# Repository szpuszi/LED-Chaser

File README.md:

# LED-Chaser
LED-Chaser is an Circular-shaped PCB, with WS2812B LEDs. It has built-in microphone so it can be reactive to music.

## How it works?
- Brain: It uses ATtiny85, which sends PWM signals to the WS2812B, receives data from the potentiometer and microphone.
- Power: We power it by USB-C.
- LEDs: The first pin of the first WS2812B receives data from ATtiny85 and forwards to the second WS2812B. The second LED does the same, all the way to the 24rd LED, it's output is floating.

# BOM
Click [here](/BOM.csv)

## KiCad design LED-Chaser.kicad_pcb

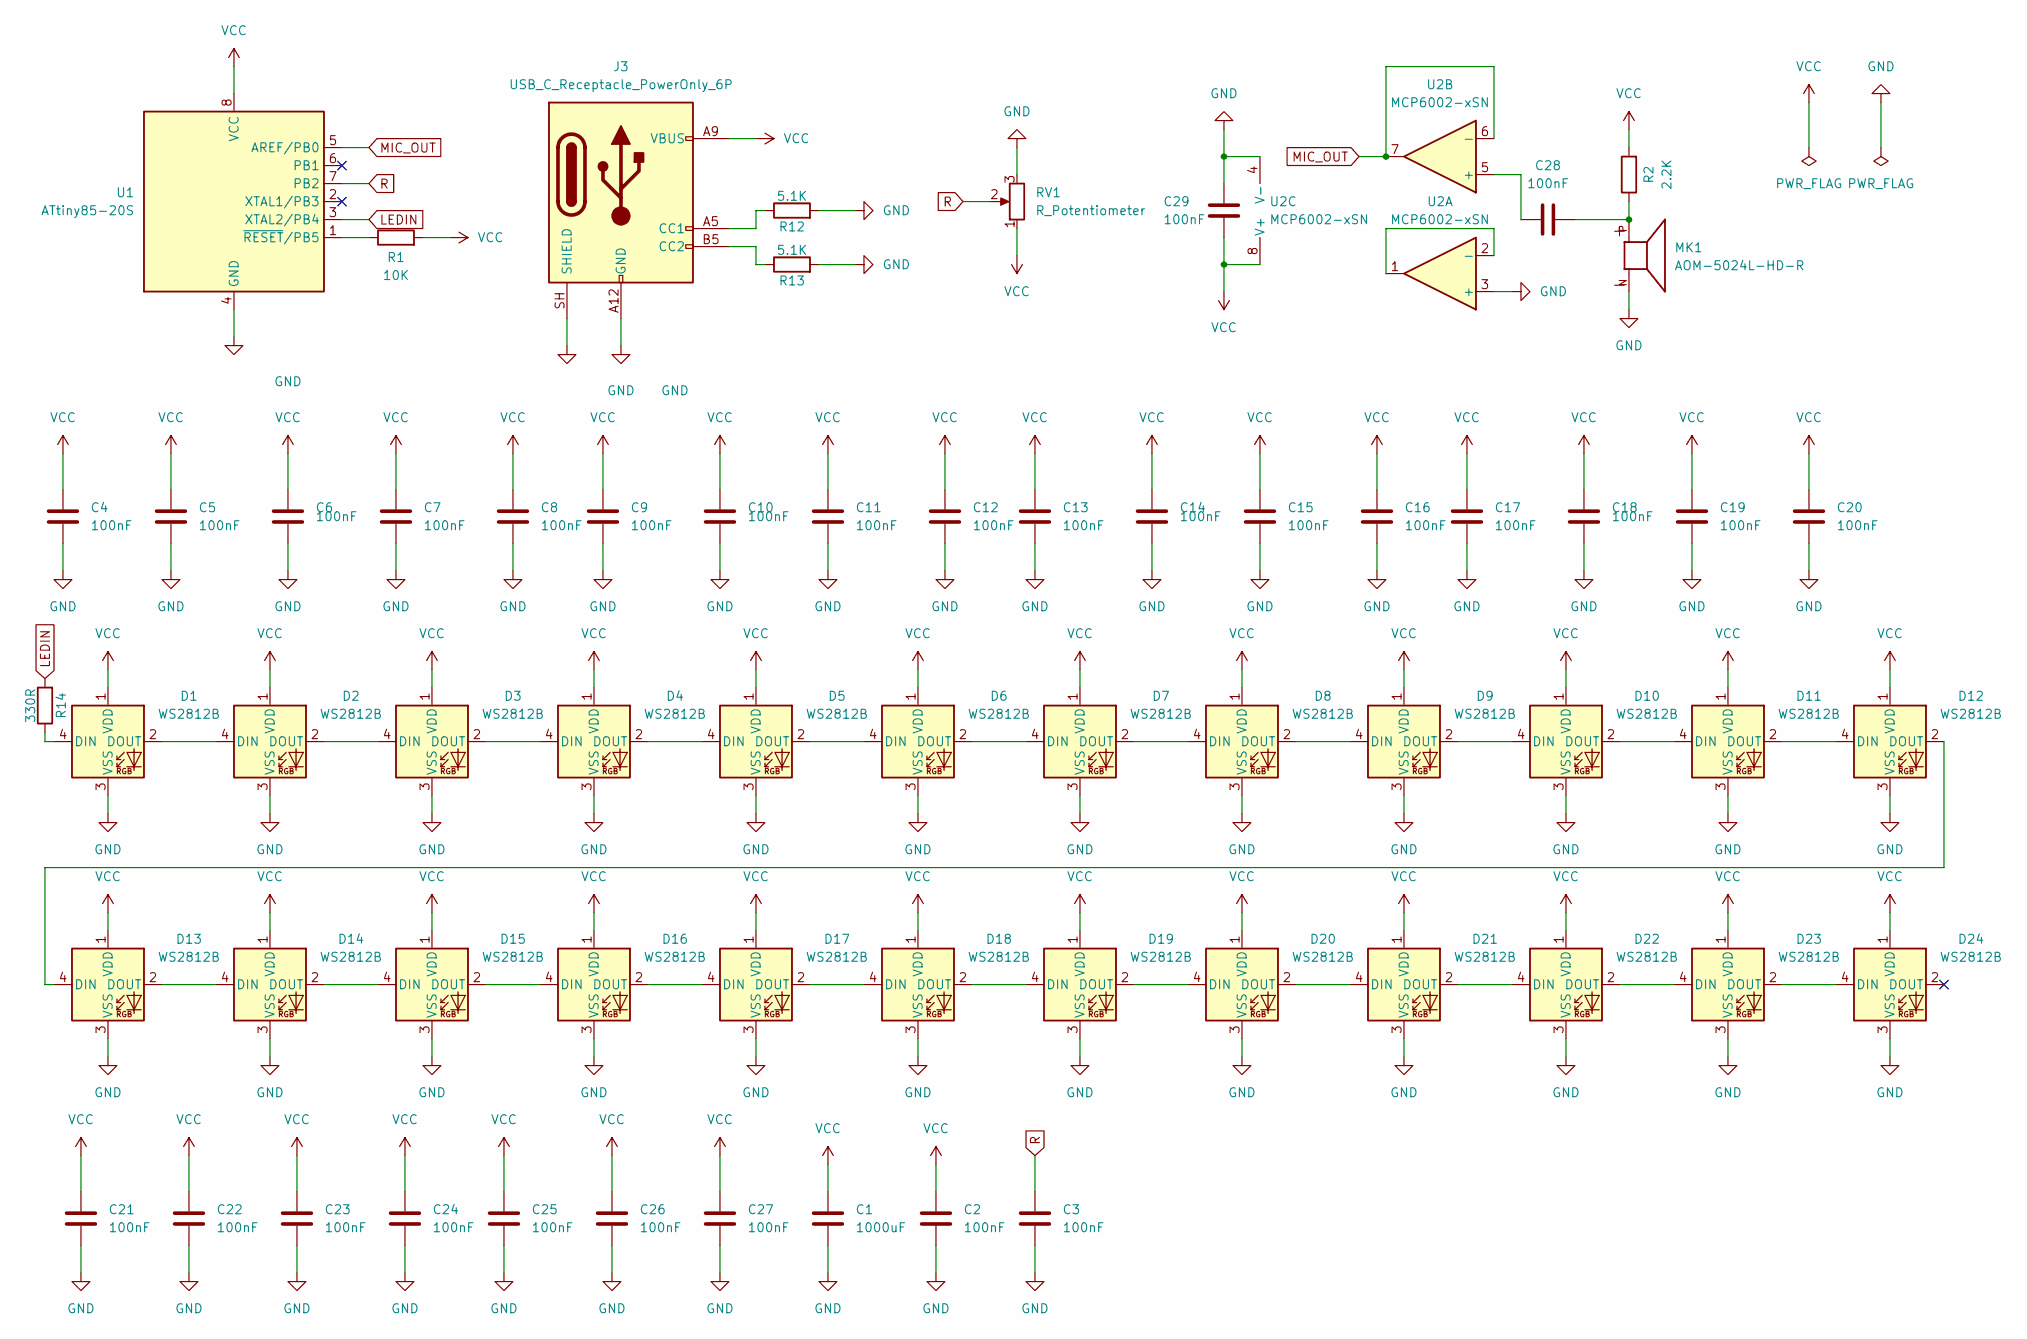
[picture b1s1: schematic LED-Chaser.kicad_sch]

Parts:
C1: 1000uF; CP_Elec_10x10.5
C2, C3, C4, C5, C6, C7, C8, C9, C10, C11, C12, C13, C14, C15, C16, C17, C18, C19, C20, C21, C22, C23, C24, C25, C26, C27, C28, C29: 100nF; C_0603_1608Metric
D1, D2, D3, D4, D5, D6, D7, D8, D9, D10, D11, D12, D13, D14, D15, D16, D17, D18, D19, D20, D21, D22, D23, D24: WS2812B; LED_WS2812B_PLCC4_5.0x5.0mm_P3.2mm
J3: USB_C_Receptacle_PowerOnly_6P; USB_C_Receptacle_GCT_USB4125-xx-x_6P_TopMnt_Horizontal
MK1: AOM-5024L-HD-R; MIC_AOM-5024L-HD-R; PARTREV A
R1: 10K; R_0603_1608Metric
R2: 2.2K; R_0603_1608Metric
R12, R13: 5.1K; R_0603_1608Metric
R14: 330R; R_0603_1608Metric
RV1: R_Potentiometer; Potentiometer_Alps_RK09K_Single_Horizontal
U1: ATtiny85-20S; SOIC-8_5.3x5.3mm_P1.27mm
U2: MCP6002-xSN; SOIC-8_3.9x4.9mm_P1.27mm

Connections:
GND: C1.2, C2.2, C3.2, C4.2, C5.2, C6.2, C7.2, C8.2, C9.2, C10.2, C11.2, C12.2, C13.2, C14.2, C15.2, C16.2, C17.2, C18.2, C19.2, C20.2, C21.2, C22.2, C23.2, C24.2, C25.2, C26.2, C27.2, C29.1, D1.3 (VSS), D2.3 (VSS), D3.3 (VSS), D4.3 (VSS), D5.3 (VSS), D6.3 (VSS), D7.3 (VSS), D8.3 (VSS), D9.3 (VSS), D10.3 (VSS), D11.3 (VSS), D12.3 (VSS), D13.3 (VSS), D14.3 (VSS), D15.3 (VSS), D16.3 (VSS), D17.3 (VSS), D18.3 (VSS), D19.3 (VSS), D20.3 (VSS), D21.3 (VSS), D22.3 (VSS), D23.3 (VSS), D24.3 (VSS), J3.A12 (GND), J3.B12 (GND), J3.SH (SHIELD), MK1.N, R12.2, R13.2, RV1.3, U1.4 (GND), U2.3 (+), U2.4 (V-)
LEDIN: R14.2, U1.3 (XTAL2/PB4)
MIC_OUT: U1.5 (AREF/PB0), U2.6 (-), U2.7
unnamed: C28.2, MK1.P, R2.1
unnamed: D1.4 (DIN), R14.1
unnamed: D1.2 (DOUT), D2.4 (DIN)
unnamed: D2.2 (DOUT), D3.4 (DIN)
unnamed: D3.2 (DOUT), D4.4 (DIN)
unnamed: D4.2 (DOUT), D5.4 (DIN)
unnamed: D5.2 (DOUT), D6.4 (DIN)
unnamed: D6.2 (DOUT), D7.4 (DIN)
unnamed: D7.2 (DOUT), D8.4 (DIN)
unnamed: D8.2 (DOUT), D9.4 (DIN)
unnamed: D9.2 (DOUT), D10.4 (DIN)
unnamed: D10.2 (DOUT), D11.4 (DIN)
unnamed: D11.2 (DOUT), D12.4 (DIN)
unnamed: D12.2 (DOUT), D13.4 (DIN)
unnamed: D13.2 (DOUT), D14.4 (DIN)
unnamed: D14.2 (DOUT), D15.4 (DIN)
unnamed: D15.2 (DOUT), D16.4 (DIN)
unnamed: D16.2 (DOUT), D17.4 (DIN)
unnamed: D17.2 (DOUT), D18.4 (DIN)
unnamed: D18.2 (DOUT), D19.4 (DIN)
unnamed: D19.2 (DOUT), D20.4 (DIN)
unnamed: D20.2 (DOUT), D21.4 (DIN)
unnamed: D21.2 (DOUT), D22.4 (DIN)
unnamed: D22.2 (DOUT), D23.4 (DIN)
unnamed: D23.2 (DOUT), D24.4 (DIN)
unnamed: J3.A5 (CC1), R12.1
unnamed: J3.B5 (CC2), R13.1
unnamed: R1.1, U1.1 (~RESET/PB5)
unnamed: U2.1, U2.2 (-)
unnamed: C28.1, U2.5 (+)
R: C3.1, RV1.2, U1.7 (PB2)
VCC: C1.1, C2.1, C4.1, C5.1, C6.1, C7.1, C8.1, C9.1, C10.1, C11.1, C12.1, C13.1, C14.1, C15.1, C16.1, C17.1, C18.1, C19.1, C20.1, C21.1, C22.1, C23.1, C24.1, C25.1, C26.1, C27.1, C29.2, D1.1 (VDD), D2.1 (VDD), D3.1 (VDD), D4.1 (VDD), D5.1 (VDD), D6.1 (VDD), D7.1 (VDD), D8.1 (VDD), D9.1 (VDD), D10.1 (VDD), D11.1 (VDD), D12.1 (VDD), D13.1 (VDD), D14.1 (VDD), D15.1 (VDD), D16.1 (VDD), D17.1 (VDD), D18.1 (VDD), D19.1 (VDD), D20.1 (VDD), D21.1 (VDD), D22.1 (VDD), D23.1 (VDD), D24.1 (VDD), J3.A9 (VBUS), J3.B9 (VBUS), R1.2, R2.2, RV1.1, U1.8 (VCC), U2.8 (V+)

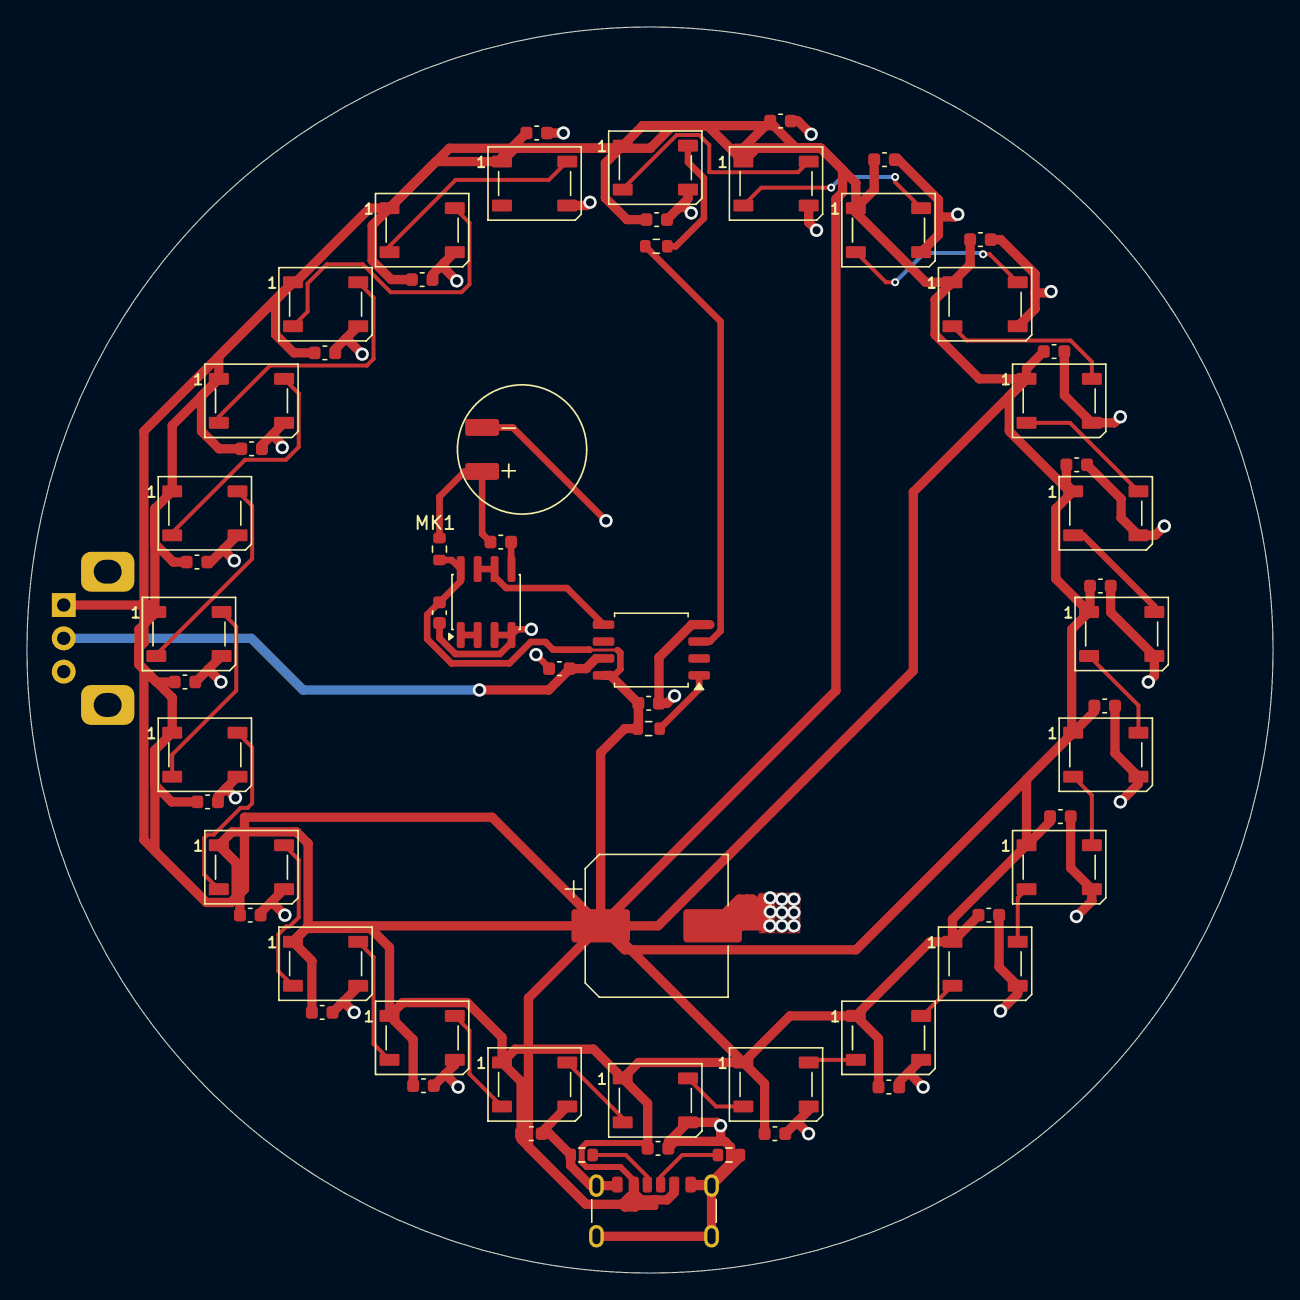
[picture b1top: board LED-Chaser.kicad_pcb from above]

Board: 2 copper layers, 93.5 x 93.5 mm, 63 parts (0 on the bottom side), 35 nets.

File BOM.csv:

Reference,Qty,Value,Link
C1,1,1000uF,https://www.tme.eu/pl/details/eeeft1c102ap/kondensatory-elek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
"C2,C3,C4,C5,C6,C7,C8,C9,C10,C11,C12,C13,C14,C15,C16,C17,C18,C19,C20,C21,C22,C23,C24,C25,C26,C27,C28,C29",28,100nF,https://www.tme.eu/pl/details/cl10b104ka8nnnc/kondensatory-m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
"D1,D2,D3,D4,D5,D6,D7,D8,D9,D10,D11,D12,D13,D14,D15,D16,D17,D18,D19,D20,D21,D22,D23,D24",24,WS2812B,https://www.tme.eu/pl/details/ws2812b-v5/diody-led-smd-kolor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
J3,1,USB_C_Receptacle_PowerOnly_6P,https://www.tme.eu/pl/details/usb4125-gf-a-0190/zlacza-usb-i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
MK1,1,AOM-5024L-HD-R,https://www.tme.eu/pl/details/aom-5024l-hd-r/mikrofony-i-slu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
R1,1,10K,https://www.tme.eu/pl/details/crcw060310k0fkea/rezystory-smd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
R2,1,2.2K,https://www.tme.eu/pl/details/crcw06032k20fkea/rezystory-smd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
"R12,R13",2,5.1K,https://www.tme.eu/pl/details/rca06035k10fkea/rezystory-smd/vishay/
R14,1,330R,https://www.tme.eu/pl/details/rca0603330rfkea/rezystory-smd/vishay/
RV1,1,R_Potentiometer,https://www.tme.eu/pl/details/rk09k1110a0j/potencjometry-jed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
U1,1,ATtiny85-20S,https://www.tme.eu/pl/details/attiny85-20sf/rodzina-avr-8-bi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
U2,1,MCP6002-xSN,https://www.tme.eu/pl/details/mcp6002-e_sn/wzmacniacze-opera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

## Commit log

2026-05-12 Rename LED-Chaser.csv to BOM.csv
